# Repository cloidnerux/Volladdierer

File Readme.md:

###proggen.org Volladdierer PCB

Dies ist die PCB Version zu dem Volladdierer von proggen.org:
https://www.proggen.org/doku.php?id=electronics:projects:adder

Schaltplan und Layout wurden mit Eagle v.7.2.0 erstellt.

Die Gerber-Files sind im Ornder Gerber zu finden, ein PDF mit Schaltplan und Layout ist unter "Volladdierer.pdf" zu finden.

Erstellt von cloidnerux.

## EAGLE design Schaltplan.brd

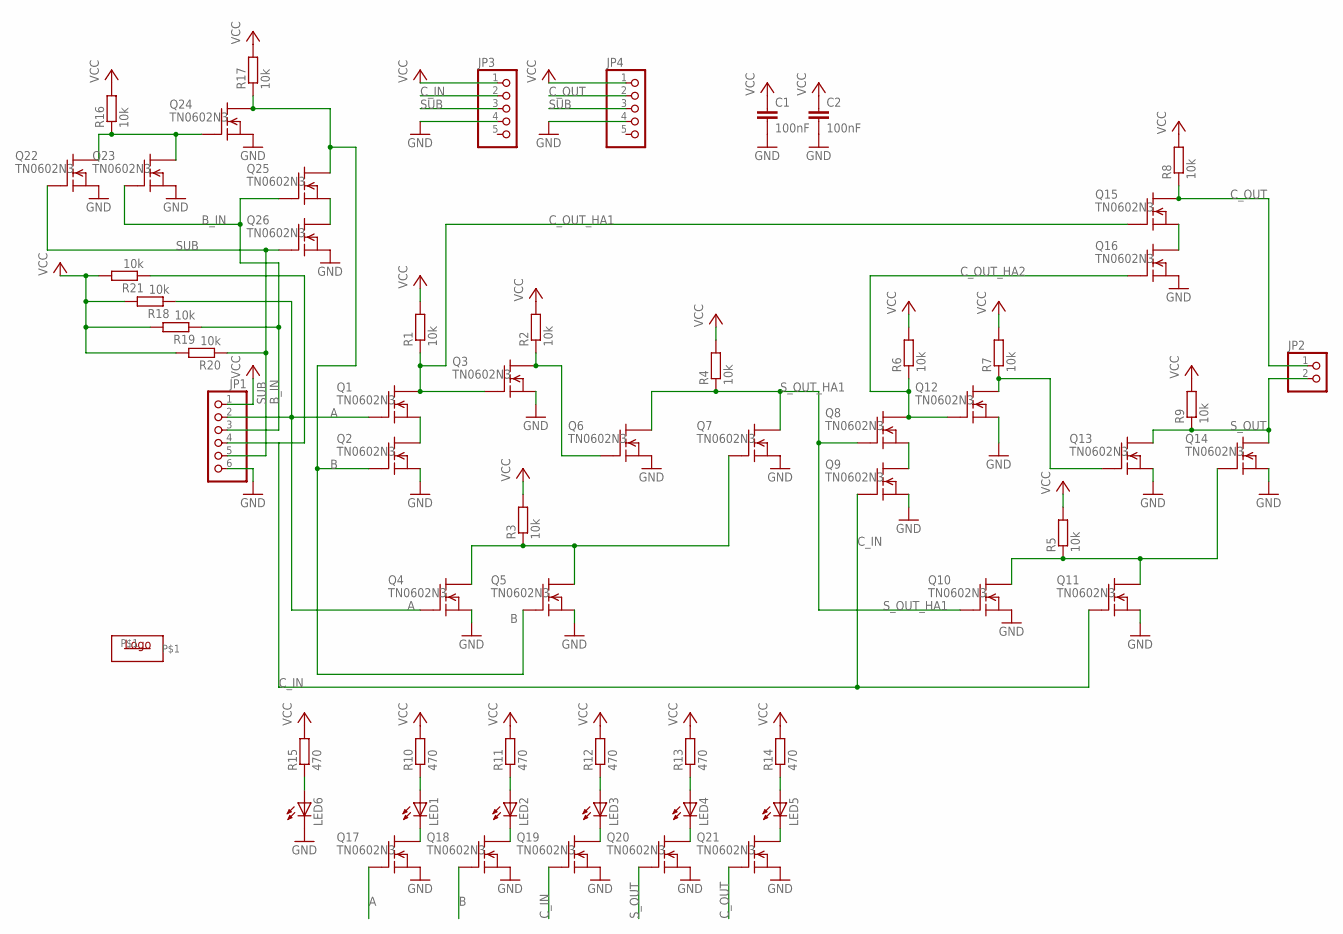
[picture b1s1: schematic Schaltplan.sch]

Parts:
C1, C2: 100nF; C025-024X044
JP1: PINHD-1X6; 1X06
JP2: PINHD-1X2; 1X02
JP3, JP4: PINHD-1X5; 1X05
LED1, LED2, LED3, LED4, LED5, LED6: LED3MM
Q1, Q2, Q3, Q4, Q5, Q6, Q7, Q8, Q9, Q10, Q11, Q12, Q13, Q14, Q15, Q16, Q17, Q18, Q19, Q20, Q21, Q22, Q23, Q24, Q25, Q26: TN0602N3; TO-92
R1, R2, R3, R4, R5, R6, R7, R8, R9, R16, R17: 10k; 0204V
R10, R11, R12, R13, R14, R15: 470; 0204V
R18, R19, R20, R21: 10k; M0805
U$3: LOGO

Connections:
A: JP1.2, Q1.2 (G), Q4.2 (G), Q17.2 (G), R18.1
B: Q2.2 (G), Q5.2 (G), Q18.2 (G), Q24.3 (D), Q25.3 (D), R17.1
B_IN: JP1.3, Q23.2 (G), Q25.2 (G), R19.1
C_IN: JP1.4, JP3.2, Q9.2 (G), Q11.2 (G), Q19.2 (G), R21.1
C_OUT: JP2.1, JP4.2, Q15.3 (D), Q21.2 (G), R8.1
C_OUT_HA1: Q1.3 (D), Q3.2 (G), Q15.2 (G), R1.1
C_OUT_HA2: Q8.3 (D), Q12.2 (G), Q16.2 (G), R6.1
GND: C1.2, C2.2, JP1.6, JP3.4, JP4.4, LED6.K (C), Q2.1 (S), Q3.1 (S), Q4.1 (S), Q5.1 (S), Q6.1 (S), Q7.1 (S), Q9.1 (S), Q10.1 (S), Q11.1 (S), Q12.1 (S), Q13.1 (S), Q14.1 (S), Q16.1 (S), Q17.1 (S), Q18.1 (S), Q19.1 (S), Q20.1 (S), Q21.1 (S), Q22.1 (S), Q23.1 (S), Q24.1 (S), Q26.1 (S)
unnamed: LED1.A, R10.1
unnamed: Q1.1 (S), Q2.3 (D)
unnamed: Q3.3 (D), Q6.2 (G), R2.1
unnamed: Q4.3 (D), Q5.3 (D), Q7.2 (G), R3.1
unnamed: LED1.K (C), Q17.3 (D)
unnamed: LED2.A, R11.1
unnamed: LED2.K (C), Q18.3 (D)
unnamed: LED3.A, R12.1
unnamed: LED3.K (C), Q19.3 (D)
unnamed: Q8.1 (S), Q9.3 (D)
unnamed: Q12.3 (D), Q13.2 (G), R7.1
unnamed: Q10.3 (D), Q11.3 (D), Q14.2 (G), R5.1
unnamed: LED4.A, R13.1
unnamed: Q15.1 (S), Q16.3 (D)
unnamed: LED4.K (C), Q20.3 (D)
unnamed: LED5.A, R14.1
unnamed: LED5.K (C), Q21.3 (D)
unnamed: LED6.A, R15.1
unnamed: Q22.3 (D), Q23.3 (D), Q24.2 (G), R16.1
unnamed: Q25.1 (S), Q26.3 (D)
SUB: JP1.5, JP3.3, JP4.3, Q22.2 (G), Q26.2 (G), R20.1
S_OUT: JP2.2, Q13.3 (D), Q14.3 (D), Q20.2 (G), R9.1
S_OUT_HA1: Q6.3 (D), Q7.3 (D), Q8.2 (G), Q10.2 (G), R4.1
VCC: C1.1, C2.1, JP1.1, JP3.1, JP4.1, R1.2, R2.2, R3.2, R4.2, R5.2, R6.2, R7.2, R8.2, R9.2, R10.2, R11.2, R12.2, R13.2, R14.2, R15.2, R16.2, R17.2, R18.2, R19.2, R20.2, R21.2

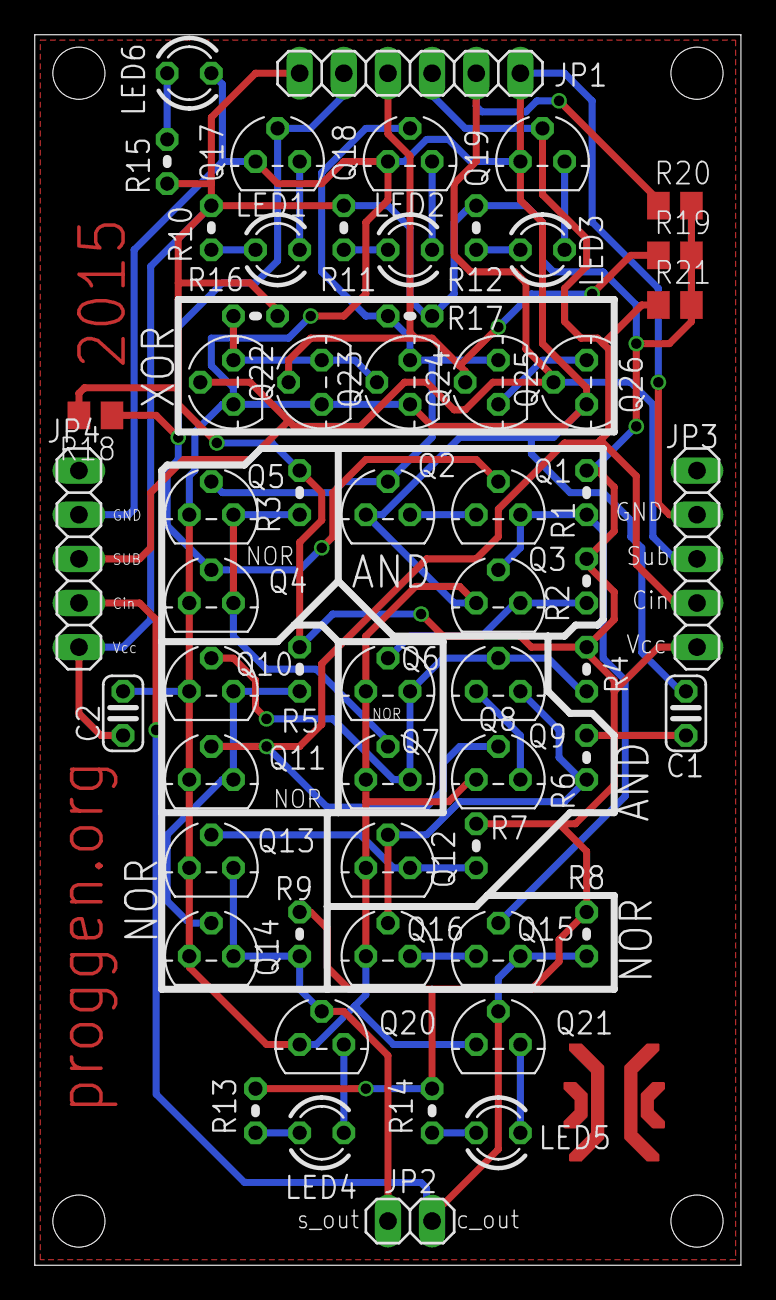
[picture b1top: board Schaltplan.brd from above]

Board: 2 copper layers, 40.6 x 70.8 mm, 60 parts (0 on the bottom side), 32 nets.

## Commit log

2015-01-21 :octocat: Added .gitattributes & .gitignore files
2015-01-21 Initial commit
    Initial commit of the full adder hardware PCB
2015-02-06 Fixed Bug: Missing connection
2015-02-12 Added Pull-Up Resistors
2015-02-12 Removed temp files
2015-02-12 Fixed error, updated pdf
